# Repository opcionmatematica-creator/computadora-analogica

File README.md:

# Computadora analógica por módulos

Reconstrucción del proyecto de **Joshua C. Johnson, "Design and Analysis of an Analog Computer: From
Concept to Final System" (Georgia Tech, 2016)** (`docs/johnson_AC.pdf`), dividido en módulos que
cualquiera puede montar y probar uno por uno, con una aplicación web/escritorio que reúne todo.

## Abrir la aplicación

- **Escritorio:** doble clic en `Computadora Analogica.vbs` (o en el acceso directo del Escritorio;
  `crear_acceso_directo.ps1` lo vuelve a crear). Se abre como ventana propia en Edge o Chrome. Con la
  app de escritorio, los botones «Abrir en KiCad» abren cada proyecto, su esquemático completo y su
  simulación.
- **App nativa (Rust):** `cargo build --release --manifest-path app/Cargo.toml` crea
  `app/target/release/computadora-analogica(.exe)`: un solo ejecutable, sin dependencias, que el
  lanzador usa si existe. Si no está compilado, el lanzador usa `node server.js` (mismo comportamiento).
- **Linux:** el ejecutable de Rust o `node server.js` abren la app en Chrome/Chromium/Edge como
  ventana propia (y se cierran con ella) o, si no hay ninguno, en el navegador predeterminado.
  «Abrir en KiCad» usa el `kicad` del PATH (hace falta KiCad 10: los proyectos son de esa versión).
- **Web:** arranca el servidor y abre http://127.0.0.1:8642/web/ en el navegador.
- **Publicar:** la carpeta es un sitio estático (`web/`, `docs/`, `simulaciones/`). Súbela tal cual a
  GitHub Pages, Netlify o similar y entra por `/web/`.

## Módulos

| # | Módulo | Fabricar | Función |
|---|--------|---------:|---------|
| M1 | Fuente ±15 V y control | 1 | Bus de 4 hilos (+15, GND, −15, OP) y conmutador IC/OPERAR (L7812 → relés) |
| M2 | Condición inicial | 2 | Potenciómetro multivuelta + seguidor LF412 |
| M3 | Integrador | 3 | Integrador sumador LF412, relé G5V-2 IC/OPERAR, C = 1 µF / 100 nF, buffer |
| M4 | Sumador inversor | 1 | −Rf·ΣVi/Ri; Rf de 10 kΩ o trimmer de 100 kΩ |
| M5 | Coeficientes | 1 | 4 potenciómetros con buffer (constantes como g = −9.8 V) |
| M6 | Filtro de salida | 1 | RC 10 kΩ/100 nF (159 Hz) con BNC X/Y al osciloscopio |
| M7 | Multiplicador | 2 | AD633, W = (X1−X2)(Y1−Y2)/10 + Z (para Lorenz) |

Programas incluidos: **caída libre** (Figs. 11–17) y **atractor de Lorenz** (Fig. 18), con diagrama
de cableado, conexiones paso a paso, simulación en KiCad del programa completo y simulador interactivo.

Cada módulo tiene en la app: esquemático **por partes** (un recorte por bloque) y **completo** (todo
con cables, sin etiquetas de red), PCB y modelo 3D con el valor, las bandas de color y la ficha de cada
pieza, **simulación hecha en KiCad** con un apartado por punto de medida (dónde va la punta y qué se
debe ver), materiales, montaje en protoboard, prueba y archivos.

## Estructura

```
hardware/gen_schematics.py   esquemáticos KiCad 10 (schlib) + verificación de netlist y ERC
hardware/gen_completos.py    esquemático completo de cada módulo (todo con cables) + hoja de simulación KiCad
hardware/gen_sim_programas.py  hojas de simulación KiCad de los programas (módulos como bloques)
hardware/export_componentes.py datos de cada pieza para el visor 3D (correr con el Python de KiCad)
hardware/gen_pcb.py          PCB por módulo (pcbnew): colocación, contorno, agujeros, serigrafía, DRC
hardware/export_assets.py    SVG/PDF/BOM/GLB/ZIP de cada módulo  ->  web/assets/<módulo>/
hardware/m*_*/               proyectos KiCad (abrir el .kicad_pro)
hardware/export_proto.py     netlist de KiCad -> montaje en protoboard (web/js/protoboard.js)
simulaciones/kicad/          simulaciones hechas en KiCad: un esquemático por módulo/programa (ver simulaciones/README.md)
tools/probar_app.mjs         prueba la app con clics reales en una sola ventana (errores, 404, imágenes rotas)
tools/verificar_protoboard.mjs  comprueba que cada protoboard tenga exactamente las conexiones del netlist
tools/capturar_protoboards.mjs  captura cada montaje paso a paso terminado -> web/assets/sistema/proto/ (Sistema completo)
web/montaje/                 montaje paso a paso de cada módulo (skill protoboard-paso-a-paso) + su .redes.json
tools/captura_ventana.ps1    captura la ventana de la app o la pantalla
blender/render_all.sh        render Cycles de cada placa  ->  web/assets/<módulo>/render.png
web/                         la aplicación (HTML + JS + three.js, sin compilación)
app/                         app de escritorio en Rust (servidor + ventana, solo biblioteca estándar)
server.js                    la misma app en Node, por si no se compila la de Rust
```

## Regenerar

```bat
python hardware\gen_schematics.py
"%LOCALAPPDATA%\Programs\KiCad\10.0\bin\python.exe" hardware\gen_pcb.py
python simulaciones\ejecutar_todo.py      (esquemáticos completos + simulaciones KiCad)
python hardware\export_assets.py
"%LOCALAPPDATA%\Programs\KiCad\10.0\bin\python.exe" hardware\export_componentes.py
python hardware\export_proto.py
node tools\capturar_protoboards.mjs   (después de cambiar un montaje de web/montaje/)
node tools\verificar_protoboard.mjs
bash blender/render_all.sh
cargo build --release --manifest-path app\Cargo.toml
```

Los `.kicad_sch` y `.kicad_pcb` son **generados**: los cambios se hacen en los scripts.
`gen_pcb.py` vuelve a colocar todas las piezas; si editas la colocación a mano en KiCad, pasa esos
cambios a la tabla `LAYOUT` antes de regenerar.

## Estado y verificación

- Esquemáticos: los 7 coinciden **exactamente** con su especificación de netlist (comprobado con el
  netlist del propio KiCad) y el **ERC sale con 0 errores**. Los 7 esquemáticos **completos** (todo con
  cables, sin etiquetas de red) tienen exactamente las mismas conexiones y también 0 errores de ERC.
- PCB: **0 violaciones de DRC** por colocación y paridad con el esquemático correcta.
  **Las pistas no están ruteadas todavía** (ver abajo).
- Simulación en KiCad (esquemáticos de `simulaciones/kicad/`, ngspice de KiCad): el integrador carga
  −2 V y luego integra a −1 V/s hasta −4.5 V a los 3 s; el sumador da −(V1 + 0.1·V2) con la tierra
  virtual a 0 V; el filtro deja 4.77 V de 5 V a 50 Hz y 0.79 V a 1 kHz. En la caída libre, la altura
  máxima es 4.551 m (teoría 4.551 m) y 4.083 m con g = 12. En Lorenz sale el atractor caótico con las
  resistencias exactas del artículo.

### Pendiente: ruteo

Las placas tienen las piezas colocadas y todas las conexiones definidas (ratsnest), pero no tienen
pistas. Hay dos opciones:
1. Rutearlas a mano en KiCad: son placas pequeñas de agujero pasante a 2 capas.
2. Usar Freerouting, que necesita instalar Java y el `.jar` de Freerouting.

Mientras tanto, cada módulo se puede montar en una placa perforada siguiendo el esquemático.

## Montaje en protoboard

Cada módulo tiene su pestaña «Protoboard» con el montaje paso a paso (`web/montaje/`). `hardware/export_proto.py` exporta
el netlist de KiCad de cada módulo y `node tools/verificar_protoboard.mjs` comprueba que no haya abiertos, cortos ni
agujeros ocupados dos veces.

## Diferencias con el diseño original

- La placa original (integrador + seguidor de IC + sumador, con dos LF412) está separada en M2, M3 y M4.
- Las entradas del integrador se nombran por su ganancia real k = 1/(R·C). El artículo llama «x0.1»
  a la entrada de 1 MΩ.
- Se añade un diodo 1N4148 en la bobina del relé y una línea OP común para todos los relés.
- Las mitades de LF412 que no se usan quedan como seguidor con la entrada a GND.
- Conectores de pines de 2.54 mm en vez de borneras, para cablear con dupont.
- En la caída libre, el signo de las constantes está elegido para que no haga falta el inversor.

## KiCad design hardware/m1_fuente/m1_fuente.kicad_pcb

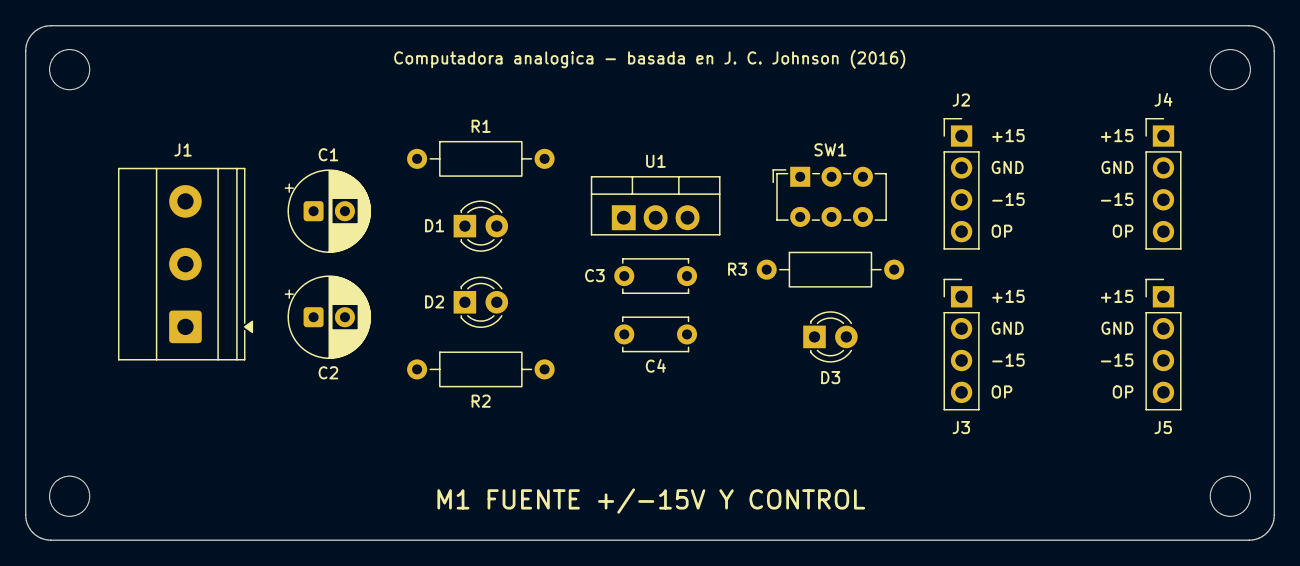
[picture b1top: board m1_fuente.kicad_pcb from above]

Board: 2 copper layers, 99.5 x 41.0 mm, 21 parts (0 on the bottom side), 8 nets, no tracks yet.

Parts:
C1, C2: 100uF 25V; CP_Radial_D6.3mm_P2.50mm
C3: 330nF; C_Disc_D5.0mm_W2.5mm_P5.00mm
C4: 100nF; C_Disc_D5.0mm_W2.5mm_P5.00mm
D1: VERDE +15V; LED_D3.0mm
D2: ROJO -15V; LED_D3.0mm
D3: AMARILLO OPERAR; LED_D3.0mm
H1, H2, H3, H4: MountingHole_3.2mm
J1: +15 / GND / -15; TerminalBlock_Phoenix_MKDS-1,5-3_1x03_P5.00mm_Horizontal
J2, J3, J4, J5: BUS; PinHeader_1x04_P2.54mm_Vertical
R1, R2: 4.7k; R_Axial_DIN0207_L6.3mm_D2.5mm_P10.16mm_Horizontal
R3: 1k; R_Axial_DIN0207_L6.3mm_D2.5mm_P10.16mm_Horizontal
SW1: IC/OPERAR; SW_E-Switch_EG1271_SPDT
U1: L7812; TO-220-3_Vertical

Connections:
+15V: C1.1, C3.1, J1.1, J2.1, J3.1, J4.1, J5.1, R1.1, U1.1
-15V: C2.2, J1.3, J2.3, J3.3, J4.3, J5.3, R2.2
/OP: J2.4, J3.4, J4.4, J5.4, R3.1, SW1.2
GND: C1.2, C2.1, C3.2, C4.2, D1.1, D2.2, D3.1, J1.2, J2.2, J3.2, J4.2, J5.2, SW1.3, U1.2
unnamed: D1.2, R1.2
unnamed: D2.1, R2.1
unnamed: D3.2, R3.2
unnamed: C4.1, SW1.1, U1.3

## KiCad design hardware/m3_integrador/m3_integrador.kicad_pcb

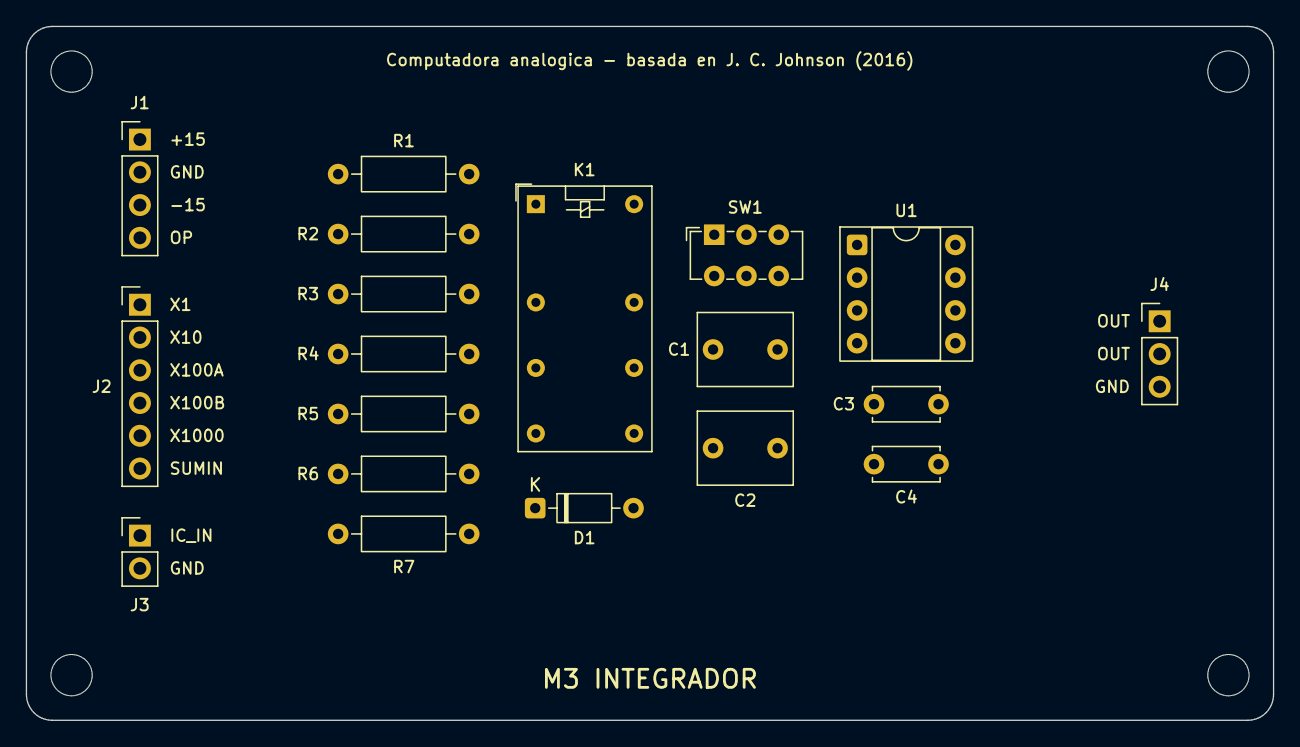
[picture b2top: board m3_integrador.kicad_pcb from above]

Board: 2 copper layers, 96.7 x 53.8 mm, 23 parts (0 on the bottom side), 17 nets, no tracks yet.

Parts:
C1: 1uF film; C_Rect_L7.2mm_W5.5mm_P5.00mm_FKS2_FKP2_MKS2_MKP2
C2: 100nF film; C_Rect_L7.2mm_W5.5mm_P5.00mm_FKS2_FKP2_MKS2_MKP2
C3, C4: 100nF; C_Disc_D5.0mm_W2.5mm_P5.00mm
D1: 1N4148; D_DO-35_SOD27_P7.62mm_Horizontal
H1, H2, H3, H4: MountingHole_3.2mm
J1: BUS; PinHeader_1x04_P2.54mm_Vertical
J2: ENTRADAS; PinHeader_1x06_P2.54mm_Vertical
J3: COND. INICIAL; PinHeader_1x02_P2.54mm_Vertical
J4: SALIDA; PinHeader_1x03_P2.54mm_Vertical
K1: G5V-2 12V; Relay_DPDT_Omron_G5V-2
R1: 1M; R_Axial_DIN0207_L6.3mm_D2.5mm_P10.16mm_Horizontal
R2: 100k; R_Axial_DIN0207_L6.3mm_D2.5mm_P10.16mm_Horizontal
R3, R4, R6, R7: 10k; R_Axial_DIN0207_L6.3mm_D2.5mm_P10.16mm_Horizontal
R5: 1k; R_Axial_DIN0207_L6.3mm_D2.5mm_P10.16mm_Horizontal
SW1: VELOCIDAD x1/x10; SW_E-Switch_EG1271_SPDT
U1: LF412; DIP-8_W7.62mm_Socket

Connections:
+15V: C3.1, J1.1, U1.8
-15V: C4.2, J1.3, U1.4
/ICN: K1.4, R6.2, R7.1
/IC_IN: J3.1, R6.1
/INV: K1.6, K1.9, SW1.2, U1.2
/IN_X1: J2.1, R1.1
/IN_X10: J2.2, R2.1
/IN_X100A: J2.3, R3.1
/IN_X100B: J2.4, R4.1
/IN_X1000: J2.5, R5.1
/OP: D1.1, J1.4, K1.1
/OUT: C1.2, C2.2, R7.2, U1.1, U1.5
/OUT_BUF: J4.1, J4.2, U1.6, U1.7
/SUMIN: J2.6, K1.13, R1.2, R2.2, R3.2, R4.2, R5.2
GND: C3.2, C4.1, D1.2, J1.2, J3.2, J4.3, K1.8, K1.11, K1.16, U1.3
unnamed: C1.1, SW1.1
unnamed: C2.1, SW1.3

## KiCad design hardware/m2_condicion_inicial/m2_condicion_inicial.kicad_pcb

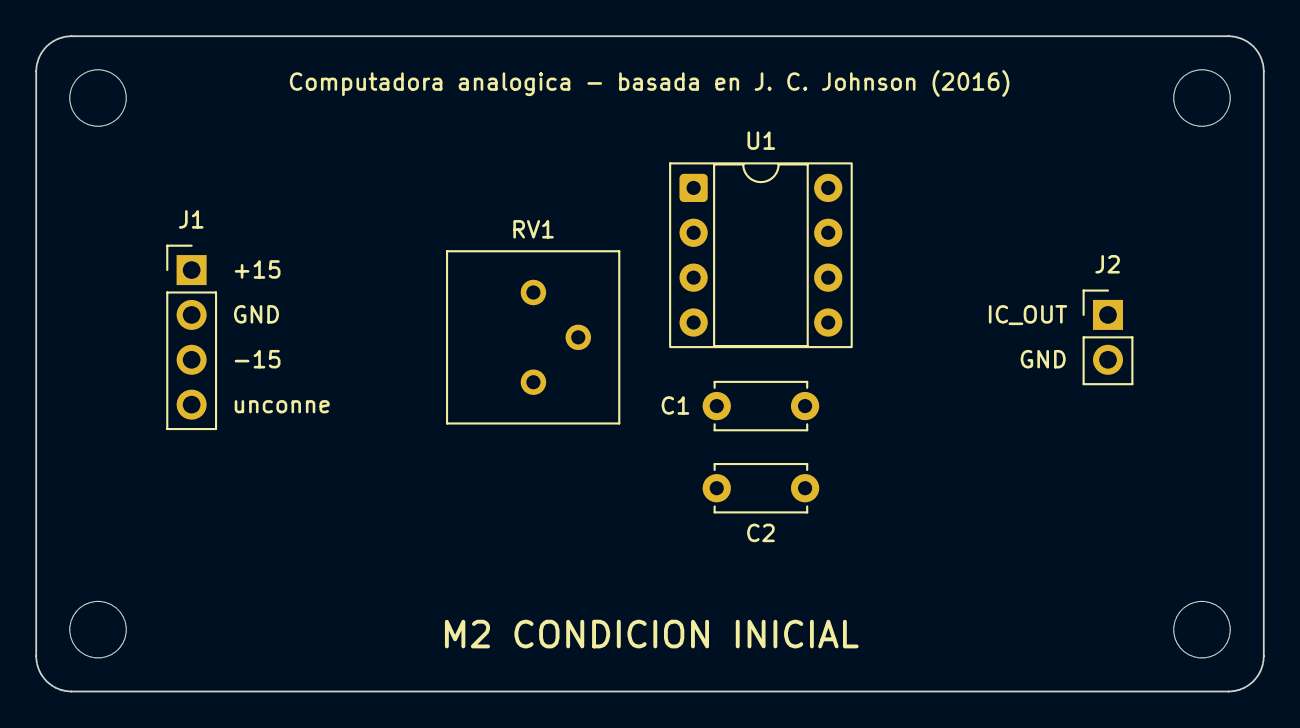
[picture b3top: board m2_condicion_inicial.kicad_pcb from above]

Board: 2 copper layers, 69.5 x 37.1 mm, 10 parts (0 on the bottom side), 6 nets, no tracks yet.

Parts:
C1, C2: 100nF; C_Disc_D5.0mm_W2.5mm_P5.00mm
H1, H2, H3, H4: MountingHole_3.2mm
J1: BUS; PinHeader_1x04_P2.54mm_Vertical
J2: -Vic; PinHeader_1x02_P2.54mm_Vertical
RV1: 10k multivuelta; Potentiometer_Bourns_3386P_Vertical
U1: LF412; DIP-8_W7.62mm_Socket

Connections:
+15V: C1.1, J1.1, RV1.3, U1.8
-15V: C2.2, J1.3, RV1.1, U1.4
/IC_OUT: J2.1, U1.1, U1.2
/WIPER: RV1.2, U1.3
GND: C1.2, C2.1, J1.2, J2.2, U1.5
unnamed: U1.6, U1.7

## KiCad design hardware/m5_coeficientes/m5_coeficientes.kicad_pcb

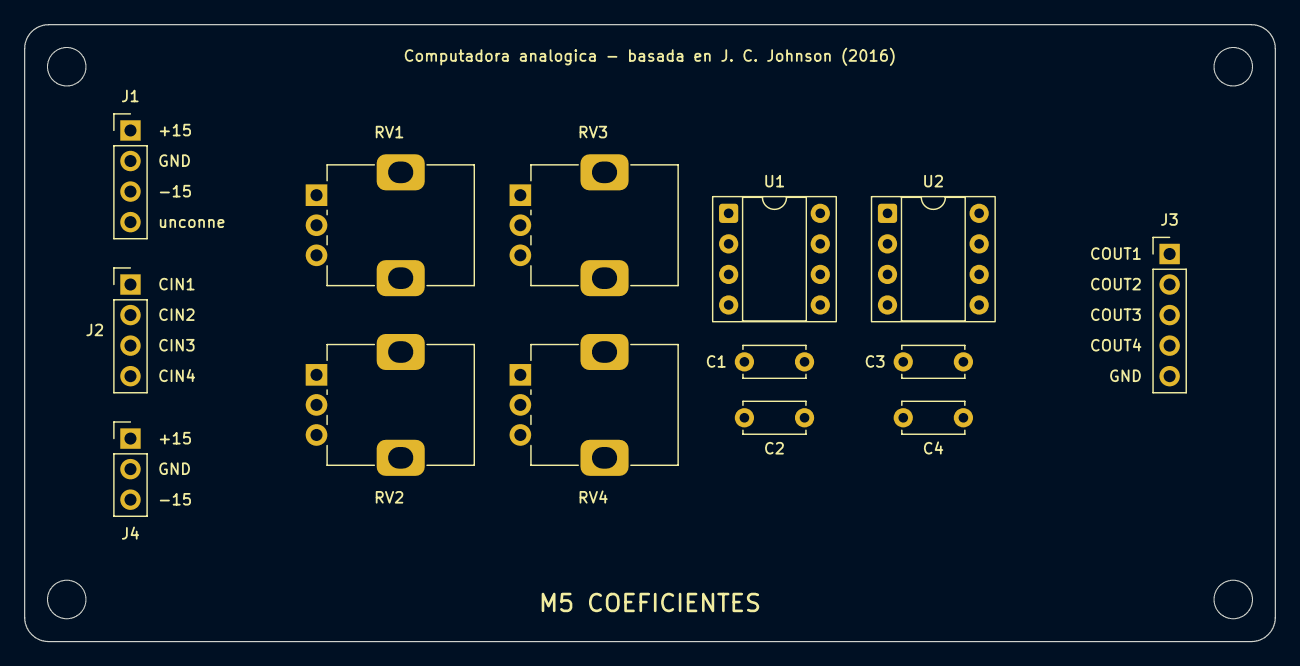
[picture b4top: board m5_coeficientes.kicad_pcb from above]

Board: 2 copper layers, 104.0 x 51.3 mm, 18 parts (0 on the bottom side), 15 nets, no tracks yet.

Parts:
C1, C2, C3, C4: 100nF; C_Disc_D5.0mm_W2.5mm_P5.00mm
H1, H2, H3, H4: MountingHole_3.2mm
J1: BUS; PinHeader_1x04_P2.54mm_Vertical
J2: ENTRADAS; PinHeader_1x04_P2.54mm_Vertical
J3: SALIDAS; PinHeader_1x05_P2.54mm_Vertical
J4: REF; PinHeader_1x03_P2.54mm_Vertical
RV1, RV2, RV3, RV4: 10k lineal; Potentiometer_Alps_RK09K_Single_Vertical
U1, U2: LF412; DIP-8_W7.62mm_Socket

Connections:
+15V: C1.1, C3.1, J1.1, J4.1, U1.8, U2.8
-15V: C2.2, C4.2, J1.3, J4.3, U1.4, U2.4
/CIN1: J2.1, RV1.3
/CIN2: J2.2, RV2.3
/CIN3: J2.3, RV3.3
/CIN4: J2.4, RV4.3
/COUT1: J3.1, U1.1, U1.2
/COUT2: J3.2, U1.6, U1.7
/COUT3: J3.3, U2.1, U2.2
/COUT4: J3.4, U2.6, U2.7
/WIP1: RV1.2, U1.3
/WIP2: RV2.2, U1.5
/WIP3: RV3.2, U2.3
/WIP4: RV4.2, U2.5
GND: C1.2, C2.1, C3.2, C4.1, J1.2, J3.5, J4.2, RV1.1, RV2.1, RV3.1, RV4.1

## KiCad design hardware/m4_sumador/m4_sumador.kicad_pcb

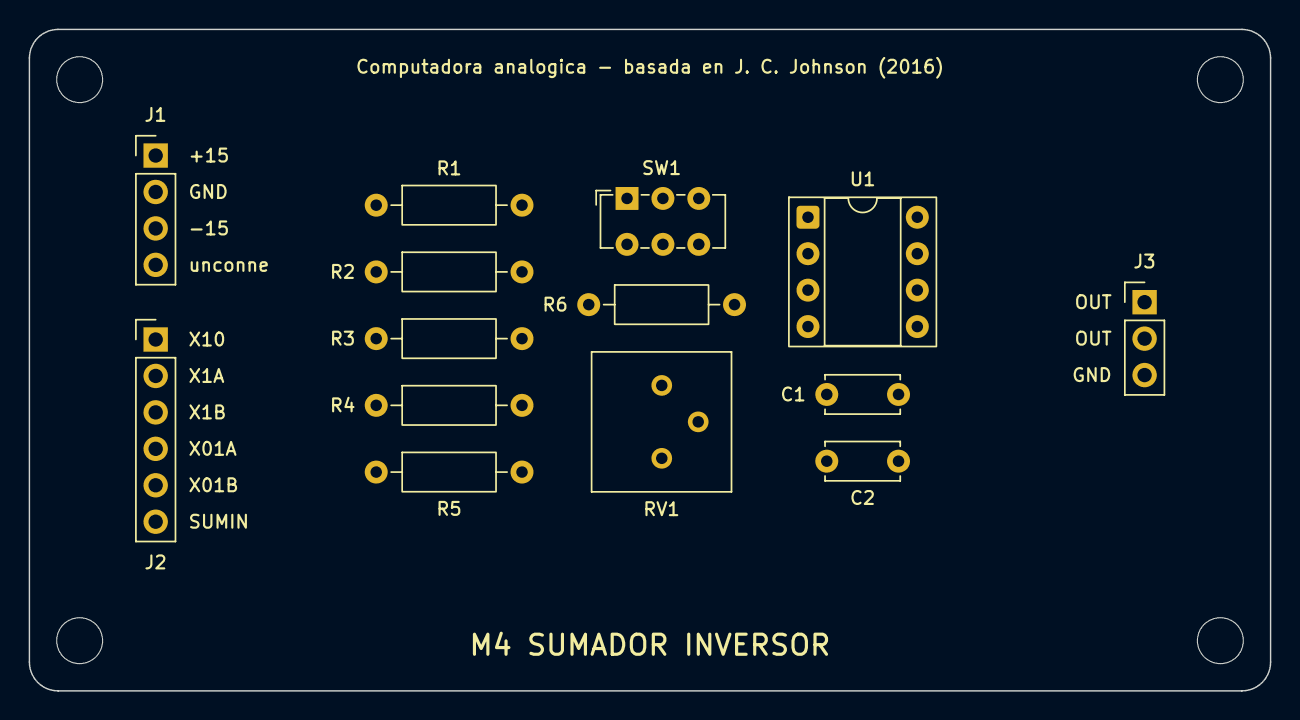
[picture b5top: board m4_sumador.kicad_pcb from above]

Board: 2 copper layers, 86.5 x 46.1 mm, 18 parts (0 on the bottom side), 13 nets, no tracks yet.

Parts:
C1, C2: 100nF; C_Disc_D5.0mm_W2.5mm_P5.00mm
H1, H2, H3, H4: MountingHole_3.2mm
J1: BUS; PinHeader_1x04_P2.54mm_Vertical
J2: ENTRADAS; PinHeader_1x06_P2.54mm_Vertical
J3: SALIDA; PinHeader_1x03_P2.54mm_Vertical
R1: 1k; R_Axial_DIN0207_L6.3mm_D2.5mm_P10.16mm_Horizontal
R2, R3, R6: 10k; R_Axial_DIN0207_L6.3mm_D2.5mm_P10.16mm_Horizontal
R4, R5: 100k; R_Axial_DIN0207_L6.3mm_D2.5mm_P10.16mm_Horizontal
RV1: 100k; Potentiometer_Bourns_3386P_Vertical
SW1: GANANCIA; SW_E-Switch_EG1271_SPDT
U1: LF412; DIP-8_W7.62mm_Socket

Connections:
+15V: C1.1, J1.1, U1.8
-15V: C2.2, J1.3, U1.4
/IN_X1A: J2.2, R2.1
/IN_X01A: J2.4, R4.1
/IN_X01B: J2.5, R5.1
/IN_X1B: J2.3, R3.1
/IN_X10: J2.1, R1.1
/OUT: J3.1, J3.2, SW1.2, U1.1
/SUMIN: J2.6, R1.2, R2.2, R3.2, R4.2, R5.2, R6.1, RV1.1, U1.2
GND: C1.2, C2.1, J1.2, J3.3, U1.3, U1.5
unnamed: R6.2, SW1.1
unnamed: RV1.3, SW1.3
unnamed: U1.6, U1.7

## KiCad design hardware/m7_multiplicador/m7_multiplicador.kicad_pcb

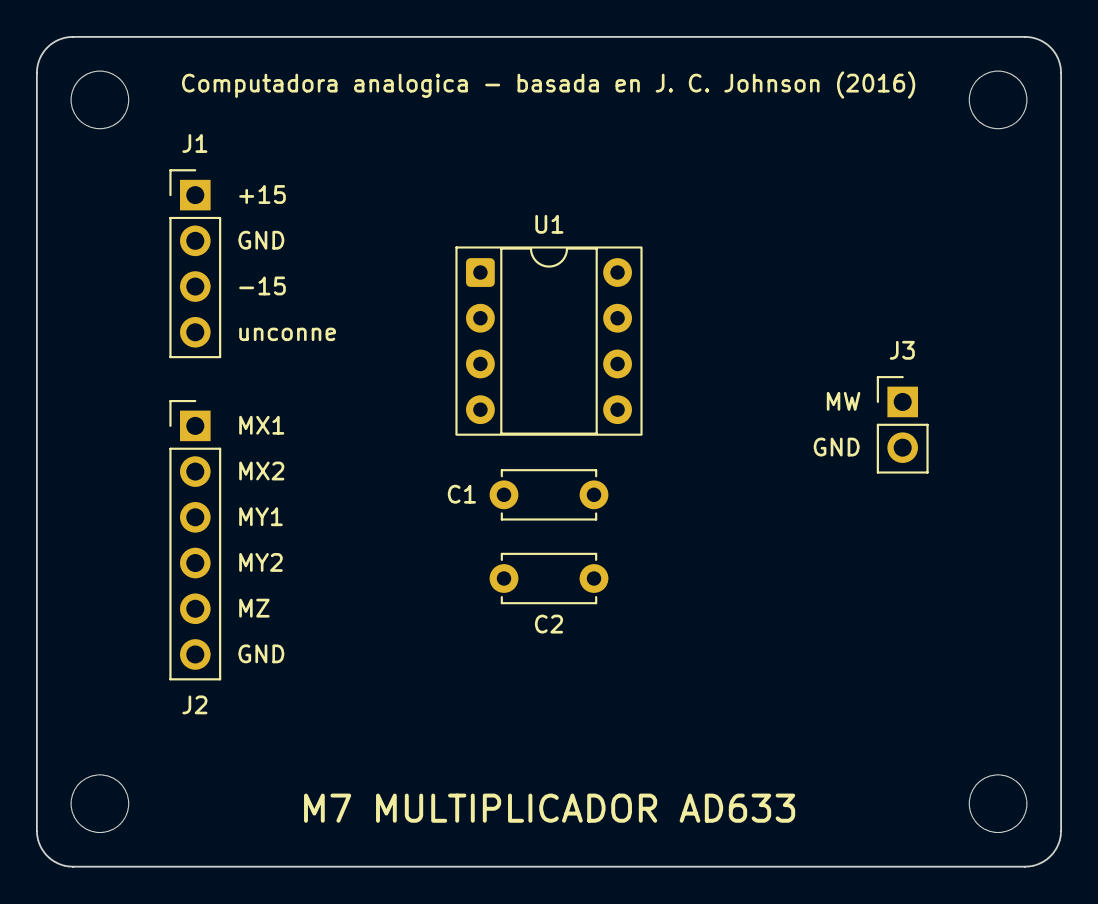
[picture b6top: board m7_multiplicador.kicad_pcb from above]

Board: 2 copper layers, 56.9 x 46.1 mm, 10 parts (0 on the bottom side), 9 nets, no tracks yet.

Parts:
C1, C2: 100nF; C_Disc_D5.0mm_W2.5mm_P5.00mm
H1, H2, H3, H4: MountingHole_3.2mm
J1: BUS; PinHeader_1x04_P2.54mm_Vertical
J2: X1 X2 Y1 Y2 Z GND; PinHeader_1x06_P2.54mm_Vertical
J3: W; PinHeader_1x02_P2.54mm_Vertical
U1: AD633JN; DIP-8_W7.62mm_Socket

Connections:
+15V: C1.1, J1.1, U1.8
-15V: C2.2, J1.3, U1.5
/MW: J3.1, U1.7
/MX1: J2.1, U1.1
/MX2: J2.2, U1.2
/MY1: J2.3, U1.3
/MY2: J2.4, U1.4
/MZ: J2.5, U1.6
GND: C1.2, C2.1, J1.2, J2.6, J3.2

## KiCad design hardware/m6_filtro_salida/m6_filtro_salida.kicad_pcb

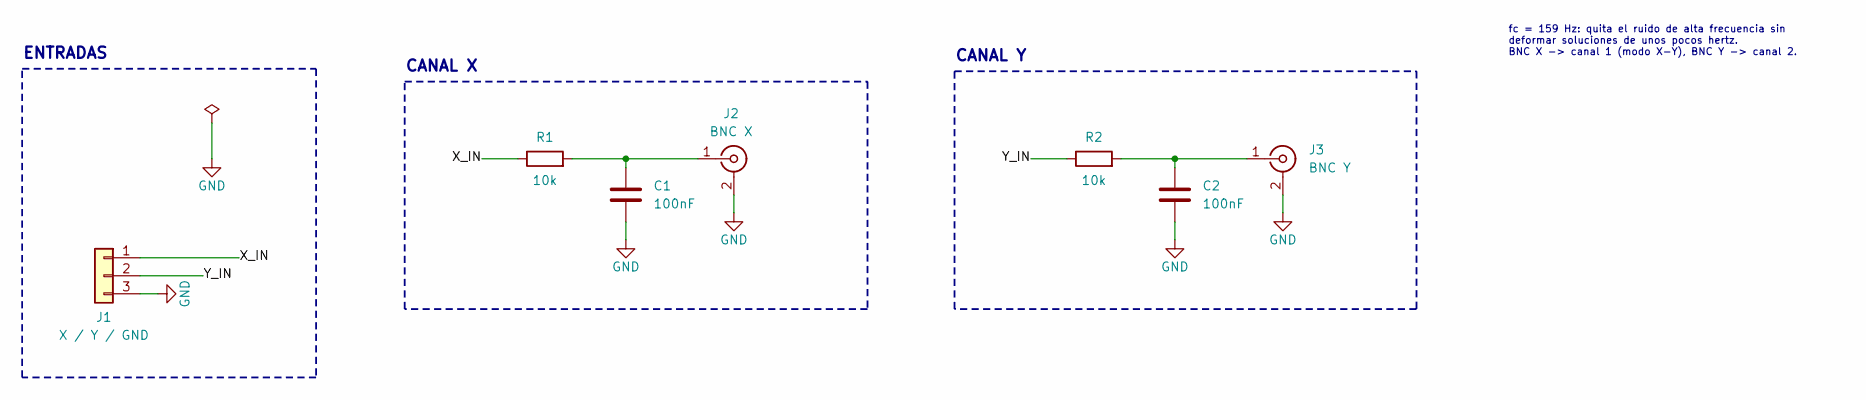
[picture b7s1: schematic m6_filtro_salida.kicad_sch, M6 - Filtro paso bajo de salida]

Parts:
C1, C2: 100nF; C_Disc_D5.0mm_W2.5mm_P5.00mm
J1: X / Y / GND; PinHeader_1x03_P2.54mm_Vertical
J2: BNC X; BNC_Amphenol_B6252HB-NPP3G-50_Horizontal
J3: BNC Y; BNC_Amphenol_B6252HB-NPP3G-50_Horizontal
R1, R2: 10k; R_Axial_DIN0207_L6.3mm_D2.5mm_P10.16mm_Horizontal

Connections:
/X_IN: J1.1, R1.1
/Y_IN: J1.2, R2.1
GND: C1.2, C2.2, J1.3, J2.2 (Ext), J3.2 (Ext)
unnamed: C1.1, J2.1 (In), R1.2
unnamed: C2.1, J3.1 (In), R2.2

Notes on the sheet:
ENTRADAS
CANAL X
CANAL Y
fc = 159 Hz: quita el ruido de alta frecuencia sin deformar soluciones de unos pocos hertz. BNC X -> canal 1 (modo X-Y), BNC Y -> canal 2.

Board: 2 copper layers, 11 parts (0 on the bottom side), 5 nets, no tracks yet.

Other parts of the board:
H1, H2, H3, H4: MountingHole_3.2mm

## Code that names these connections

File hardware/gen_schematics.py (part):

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        s.stub("RV1", 3, G, power="+15V")
        w = s.pin("RV1", 2)
        s.wire(w, (w[0] + 5.08, w[1]))
        s.label("WIPER", w[0] + 5.08, w[1])
        s.note("Gire hasta leer en el voltímetro\n-Vic (la condición inicial negada).", 55.88, 76.2, 1.0)
    with s.block("SEGUIDOR (aislamiento)"):
        follower(s, "U1", 1, 116.84, 60.96, "WIPER", "IC_OUT")
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            s.wire(b, (bus_x, b[1]))
        yA = y0 + 5 * 10.16
        s.wire((bus_x - 12.7, yA), (bus_x, yA))
        s.label("SUMIN", bus_x - 12.7, yA, angle=180)
        s.wire((bus_x, y0), (bus_x, yA))
        s.wire((bus_x, y0), (bus_x + 7.62, y0))
        s.label("SUMIN", bus_x + 7.62, y0)
        s.note("Ganancia de cada entrada con C1 = 1 uF:\n"
               "k = 1/(Ri*C): 1M -> 1/s, 100k -> 10/s,\n"
               "10k -> 100/s, 1k -> 1000/s.  Con C2 (100 nF) x10.",
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        a, b = place2(s, "D1", "Diode:1N4148", "1N4148", dx, ky, 1, FP["D"])
        s.wire(a, (dx, c1[1]), c1)
        s.wire(b, (dx, c16[1]), c16)
        s.stub("K1", 4, 5.08, label="ICN")       # COM1
        s.stub("K1", 6, 5.08, label="INV")       # NC1 (reposo = IC)
        s.stub("K1", 8, 10.16, power="GND")      # NO1
        s.stub("K1", 13, 5.08, label="SUMIN")    # COM2
        s.stub("K1", 11, 10.16, power="GND")     # NC2
        s.stub("K1", 9, 5.08, label="INV")       # NO2 (activado = OPERAR)
        s.note("Relé en reposo (OP = 0 V): IC. ICN -> INV, entradas a GND.\n"
               "Relé activado (OP = +12 V): OPERAR. ICN -> GND, entradas -> INV.",
               kx - 22.86, ky + 20.32, 1.0)
    with s.block("CONDICIÓN INICIAL (R6 / R7)"):
        a, b = place2(s, "R6", "Device:R", "10k", 66.04, 152.4, 1, FP["R"], horizontal=True)
        s.wire(a, (a[0] - 5.08, a[1]))
        s.label("IC_IN", a[0] - 5.08, a[1], angle=180)
        s.wire(b, (b[0] + 7.62, b[1]))
        s.label("ICN", b[0] + 7.62, b[1])
        a2, b2 = place2(s, "R7", "Device:R", "10k", b[0] + 20.32, 152.4, 1, FP["R"], horizontal=True)
        s.wire(a2, (b[0] + 7.62, a2[1]))
        s.wire(b2, (b2[0] + 5.08, b2[1]))
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        s.stub("U1", 3, G, power="GND", unit=1)
        m, o = s.pin("U1", 2, 1), s.pin("U1", 1, 1)
        s.wire(m, (m[0] - 7.62, m[1]))
        s.label("INV", m[0] - 7.62, m[1], angle=180)
        s.wire(o, (o[0] + 10.16, o[1]))
        s.label("OUT", o[0] + 10.16, o[1])
        # selector de velocidad: SW1 B (común) en INV, A -> C1, C -> C2
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                props={"Footprint": FP["SW"]})
        sa, sb, sc = s.pin("SW1", 1), s.pin("SW1", 2), s.pin("SW1", 3)
        s.wire(sb, (sb[0] - 5.08, sb[1]))
        s.label("INV", sb[0] - 5.08, sb[1], angle=180)
        top, bot = (sa, sc) if sa[1] < sc[1] else (sc, sa)
        ca, cb = place2(s, "C1", "Device:C", "1uF film", top[0] + 10.16, top[1], 1, FP["CF"], horizontal=True)
        s.wire(top, ca)
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            s.wire(b, (bus_x, b[1]))
        yA = y0 + 5 * 10.16
        s.wire((bus_x - 12.7, yA), (bus_x, yA))
        s.label("SUMIN", bus_x - 12.7, yA, angle=180)
        s.wire((bus_x, y0), (bus_x, yA))
        ux, uy = bus_x + 22.86, y0 + 17.78
        s.place("U1", OPAMP, "LF412", ux, uy, unit=1, props={"Footprint": FP["DIP8"]})
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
